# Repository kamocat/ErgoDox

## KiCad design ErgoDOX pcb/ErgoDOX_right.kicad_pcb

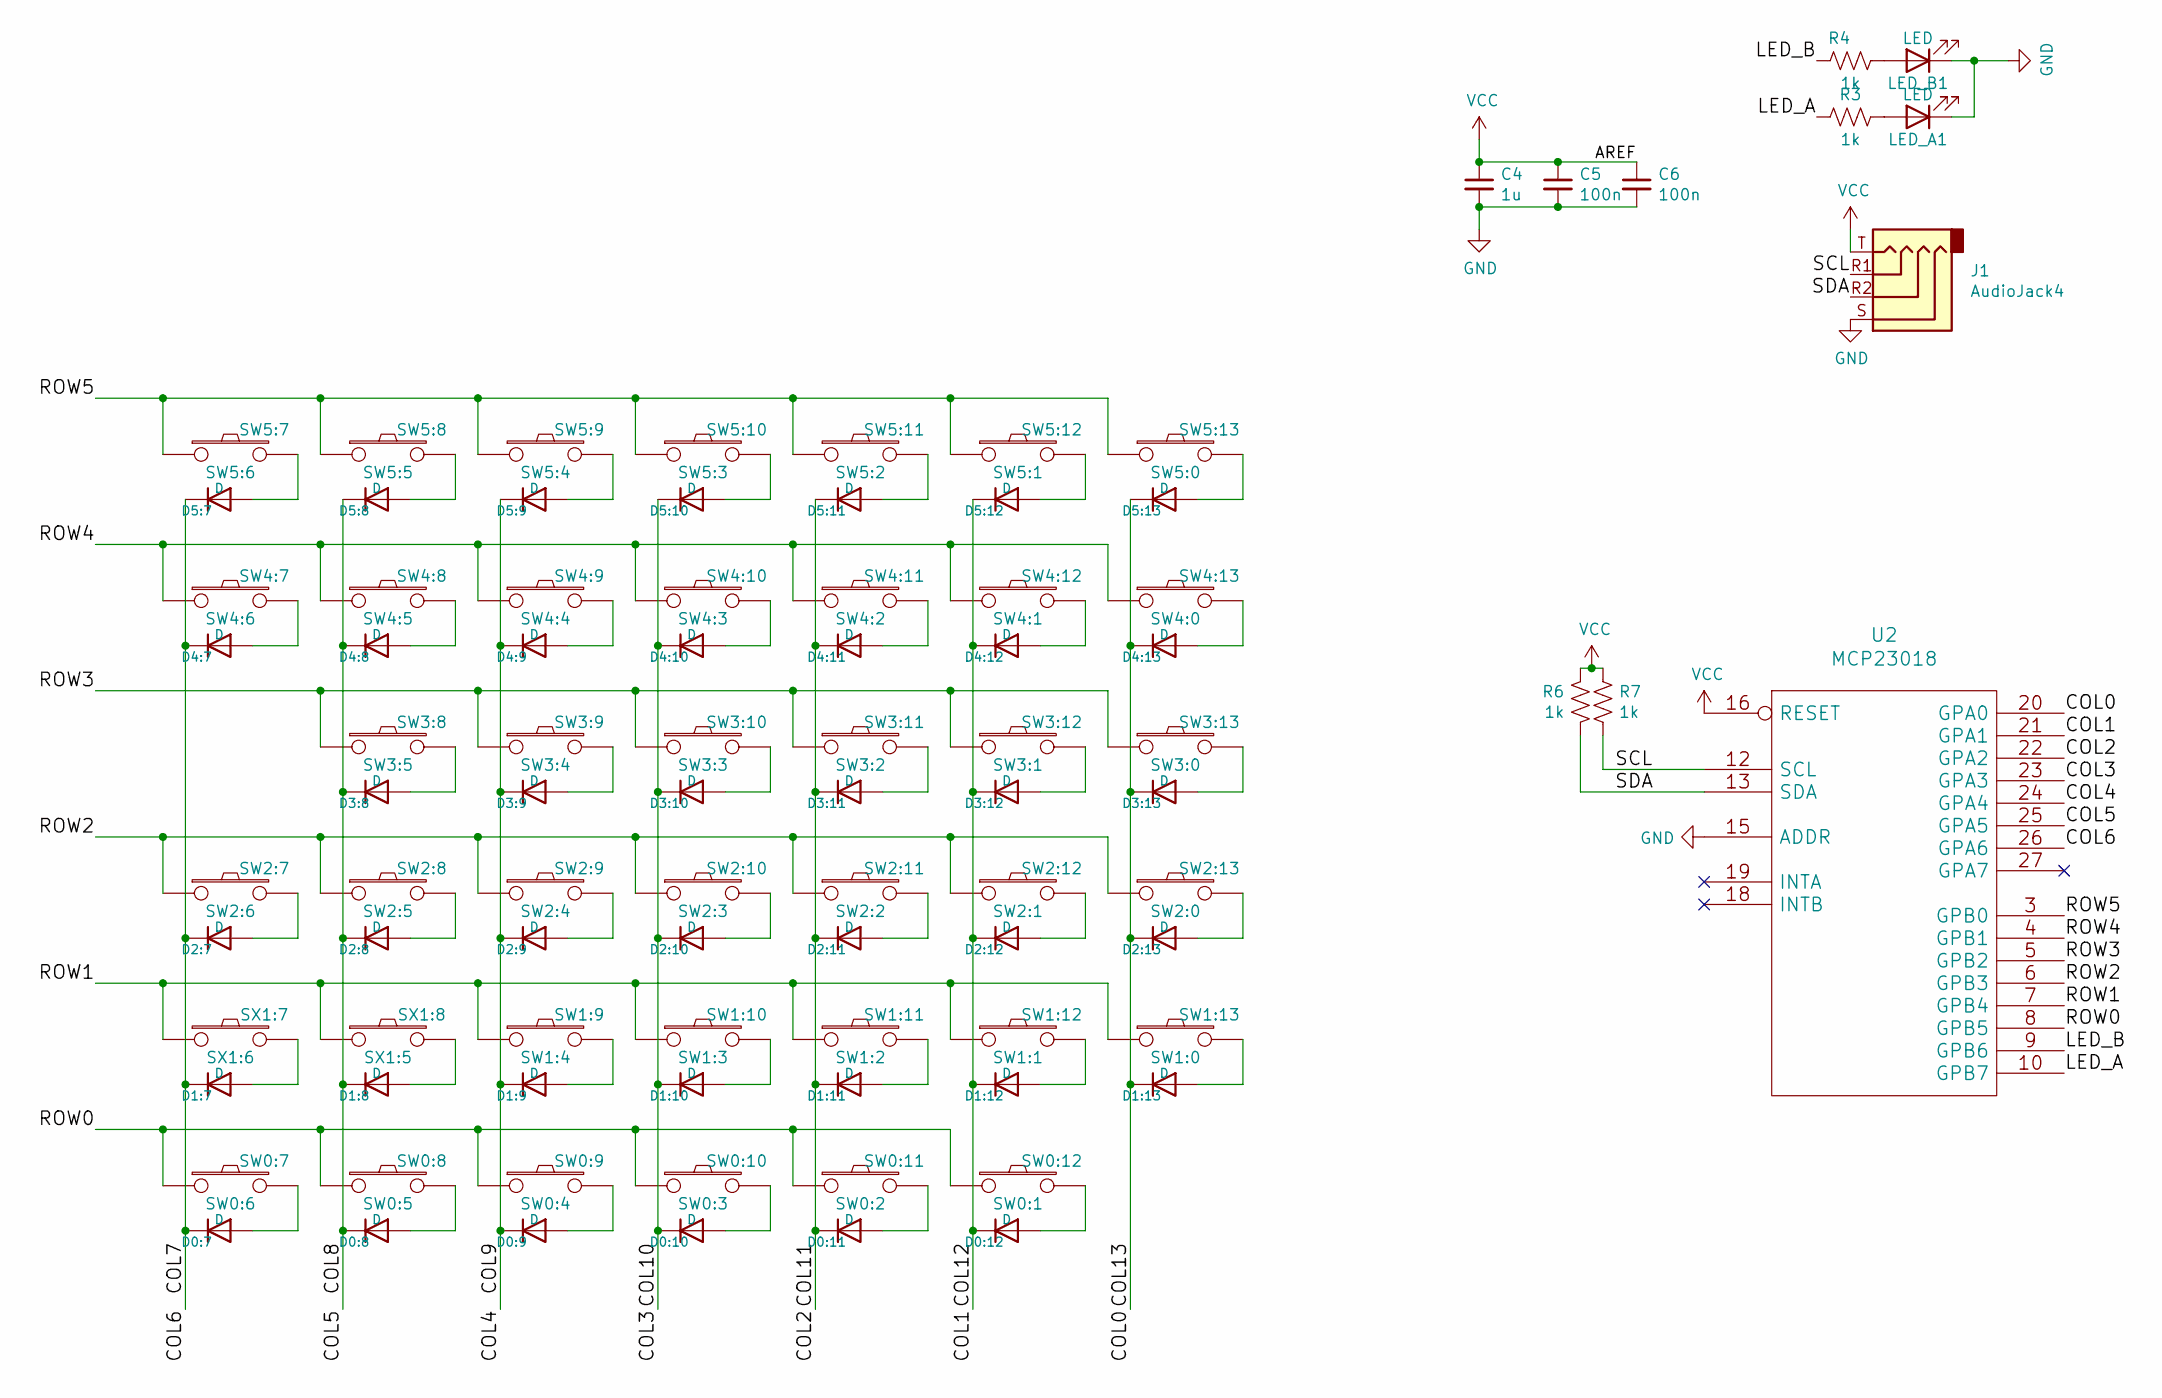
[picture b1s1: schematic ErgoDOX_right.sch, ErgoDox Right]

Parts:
C4: 1u; C_0603
C5, C6: 100n; C_0603
D0:7, D0:8, D0:9, D0:10, D0:11, D0:12, D1:7, D1:8, D1:9, D1:10, D1:11, D1:12, D1:13, D2:7, D2:8, D2:9, D2:10, D2:11, D2:12, D2:13, D3:8, D3:9, D3:10, D3:11, D3:12, D3:13, D4:7, D4:8, D4:9, D4:10, D4:11, D4:12, D4:13, D5:7, D5:8, D5:9, D5:10, D5:11, D5:12, D5:13: D; D_SOD-123
J1: AudioJack4; 54-00174
LED_A1: LED; LED_0603
LED_B1: LED; LED_0603
R3, R4, R6, R7: 1k; R_0603
SW0:7: SW0:6; MX_TOP
SW0:8: SW0:5; MX_TOP
SW0:9: SW0:4; MX_TOP
SW0:10: SW0:3; MX_TOP
SW0:11: SW0:2; MX_TOP
SW0:12: SW0:1; MX_TOP
SW1:9: SW1:4; MX_TOP
SW1:10: SW1:3; MX_TOP
SW1:11: SW1:2; MX_TOP
SW1:12: SW1:1; MX_TOP
SW1:13: SW1:0; MX_TOP
SW2:7: SW2:6; MX_TOP
SW2:8: SW2:5; MX_TOP
SW2:9: SW2:4; MX_TOP
SW2:10: SW2:3; MX_TOP
SW2:11: SW2:2; MX_TOP
SW2:12: SW2:1; MX_TOP
SW2:13: SW2:0; MX_TOP
SW3:8: SW3:5; MX_TOP
SW3:9: SW3:4; MX_TOP
SW3:10: SW3:3; MX_TOP
SW3:11: SW3:2; MX_TOP
SW3:12: SW3:1; MX_TOP
SW3:13: SW3:0; MX_TOP
SW4:7: SW4:6; MX_TOP
SW4:8: SW4:5; MX_TOP
SW4:9: SW4:4; MX_TOP
SW4:10: SW4:3; MX_TOP
SW4:11: SW4:2; MX_TOP
SW4:12: SW4:1; MX_TOP
SW4:13: SW4:0; MX_TOP
SW5:7: SW5:6; MX_TOP
SW5:8: SW5:5; MX_TOP
SW5:9: SW5:4; MX_TOP
SW5:10: SW5:3; MX_TOP
SW5:11: SW5:2; MX_TOP
SW5:12: SW5:1; MX_TOP
SW5:13: SW5:0; MX_TOP
SX1:7: SX1:6; MX_TOP
SX1:8: SX1:5; MX_TOP
U2: MCP23018; SOIC-28W_7.5x17.9mm_Pitch1.27mm

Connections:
/COL0: D1:13.1 (K), D2:13.1 (K), D3:13.1 (K), D4:13.1 (K), D5:13.1 (K), U2.20 (GPA0)
/COL1: D0:12.1 (K), D1:12.1 (K), D2:12.1 (K), D3:12.1 (K), D4:12.1 (K), D5:12.1 (K), U2.21 (GPA1)
/COL4: D0:9.1 (K), D1:9.1 (K), D2:9.1 (K), D3:9.1 (K), D4:9.1 (K), D5:9.1 (K), U2.24 (GPA4)
/COL5: D0:8.1 (K), D1:8.1 (K), D2:8.1 (K), D3:8.1 (K), D4:8.1 (K), D5:8.1 (K), U2.25 (GPA5)
/COL6: D0:7.1 (K), D1:7.1 (K), D2:7.1 (K), D4:7.1 (K), D5:7.1 (K), U2.26 (GPA6)
/COL10: D0:10.1 (K), D1:10.1 (K), D2:10.1 (K), D3:10.1 (K), D4:10.1 (K), D5:10.1 (K), U2.23 (GPA3)
/COL11: D0:11.1 (K), D1:11.1 (K), D2:11.1 (K), D3:11.1 (K), D4:11.1 (K), D5:11.1 (K), U2.22 (GPA2)
/LED_A: R3.1, U2.10 (GPB7)
/LED_B: R4.1, U2.9 (GPB6)
/ROW0: SW0:7.1, SW0:8.1, SW0:9.1, SW0:10.1, SW0:11.1, SW0:12.1, U2.8 (GPB5)
/ROW1: SW1:9.1, SW1:10.1, SW1:11.1, SW1:12.1, SW1:13.1, SX1:7.1, SX1:8.1, U2.7 (GPB4)
/ROW2: SW2:7.1, SW2:8.1, SW2:9.1, SW2:10.1, SW2:11.1, SW2:12.1, SW2:13.1, U2.6 (GPB3)
/ROW3: SW3:8.1, SW3:9.1, SW3:10.1, SW3:11.1, SW3:12.1, SW3:13.1, U2.5 (GPB2)
/ROW4: SW4:7.1, SW4:8.1, SW4:9.1, SW4:10.1, SW4:11.1, SW4:12.1, SW4:13.1, U2.4 (GPB1)
/ROW5: SW5:7.1, SW5:8.1, SW5:9.1, SW5:10.1, SW5:11.1, SW5:12.1, SW5:13.1, U2.3 (GPB0)
/SCL: J1.R1, R7.2, U2.12 (SCL)
/SDA: J1.R2, R6.1, U2.13 (SDA)
GND: C4.2, C5.2, C6.2, J1.S, LED_A1.1 (K), LED_B1.1 (K), U2.1 (GND), U2.15 (ADDR)
unnamed: D0:7.2 (A), SW0:7.2
unnamed: D0:8.2 (A), SW0:8.2
unnamed: D0:9.2 (A), SW0:9.2
unnamed: D0:10.2 (A), SW0:10.2
unnamed: D0:11.2 (A), SW0:11.2
unnamed: D0:12.2 (A), SW0:12.2
unnamed: D1:7.2 (A), SX1:7.2
unnamed: D1:8.2 (A), SX1:8.2
unnamed: D1:9.2 (A), SW1:9.2
unnamed: D1:10.2 (A), SW1:10.2
unnamed: D1:11.2 (A), SW1:11.2
unnamed: D1:12.2 (A), SW1:12.2
unnamed: D1:13.2 (A), SW1:13.2
unnamed: D2:7.2 (A), SW2:7.2
unnamed: D2:8.2 (A), SW2:8.2
unnamed: D2:9.2 (A), SW2:9.2
unnamed: D2:10.2 (A), SW2:10.2
unnamed: D2:11.2 (A), SW2:11.2
unnamed: D2:12.2 (A), SW2:12.2
unnamed: D2:13.2 (A), SW2:13.2
unnamed: D3:8.2 (A), SW3:8.2
unnamed: D3:9.2 (A), SW3:9.2
unnamed: D3:10.2 (A), SW3:10.2
unnamed: D3:11.2 (A), SW3:11.2
unnamed: D3:12.2 (A), SW3:12.2
unnamed: D3:13.2 (A), SW3:13.2
unnamed: D4:7.2 (A), SW4:7.2
unnamed: D4:8.2 (A), SW4:8.2
unnamed: D4:9.2 (A), SW4:9.2
unnamed: D4:10.2 (A), SW4:10.2
unnamed: D4:11.2 (A), SW4:11.2
unnamed: D4:12.2 (A), SW4:12.2
unnamed: D4:13.2 (A), SW4:13.2
unnamed: D5:7.2 (A), SW5:7.2
unnamed: D5:8.2 (A), SW5:8.2
unnamed: D5:9.2 (A), SW5:9.2
unnamed: D5:10.2 (A), SW5:10.2
unnamed: D5:11.2 (A), SW5:11.2
unnamed: D5:12.2 (A), SW5:12.2
unnamed: D5:13.2 (A), SW5:13.2
unnamed: LED_A1.2 (A), R3.2
unnamed: LED_B1.2 (A), R4.2
VCC: C4.1, C5.1, C6.1, J1.T, R6.2, R7.1, U2.11 (VCC), U2.16 (RESET)

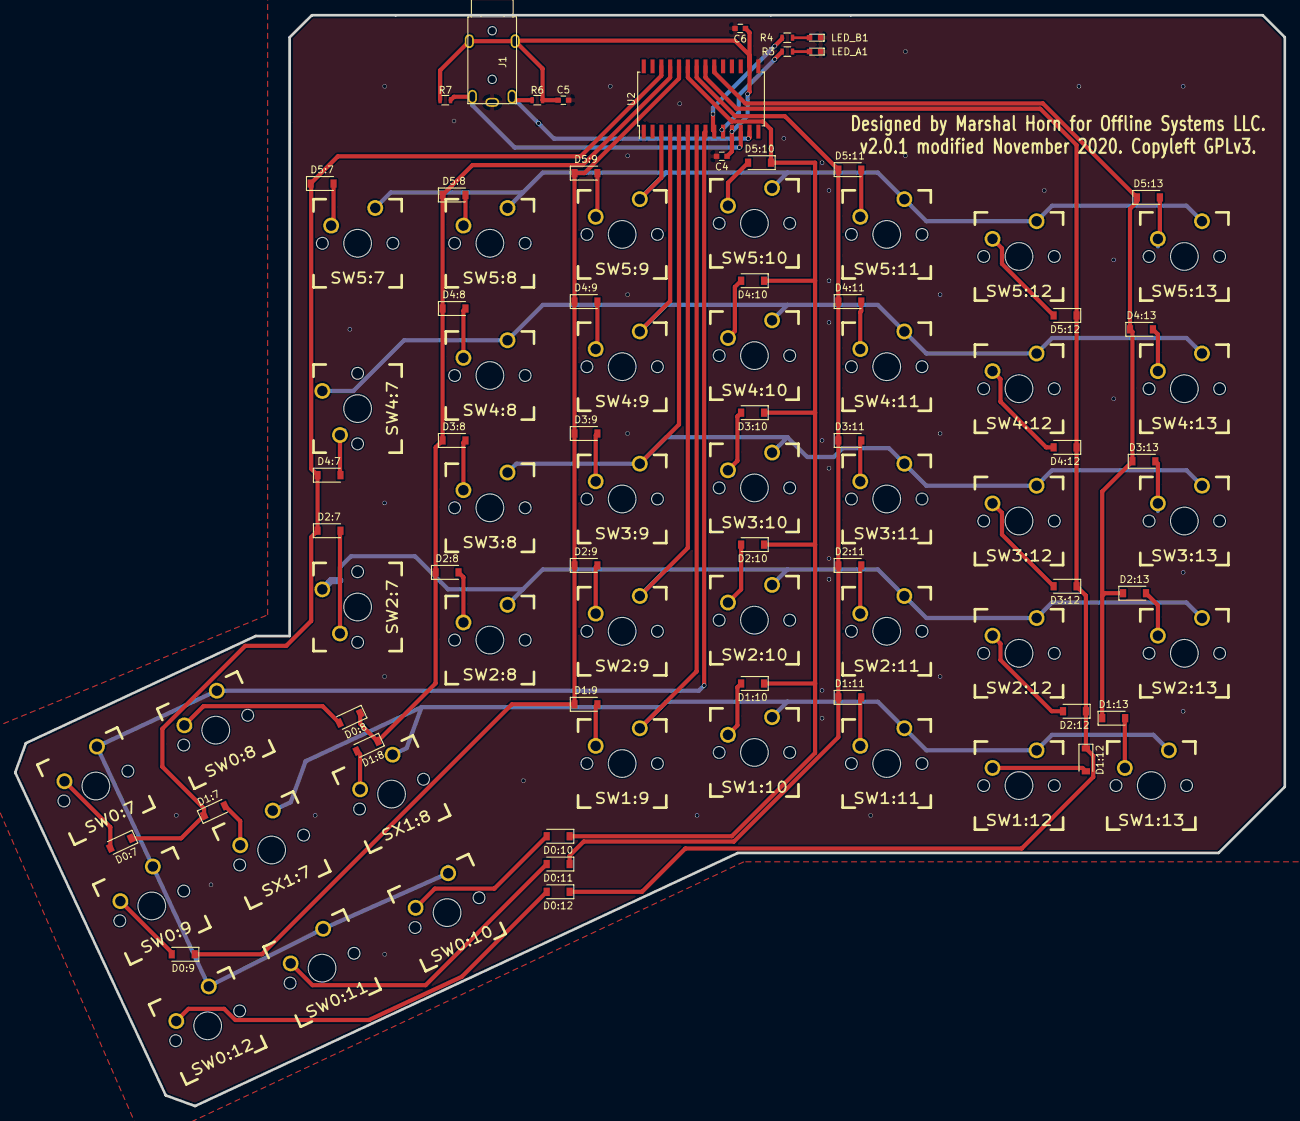
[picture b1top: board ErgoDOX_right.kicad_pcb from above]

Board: 2 copper layers, 182.8 x 157.1 mm, 91 parts (0 on the bottom side), 61 nets.

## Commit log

2020-09-17 Replaced teensy with atmega
    Imported project into new version of KiCad
    Initial routing of traces is done
    Switch footprints need some investigation - overlap is throwing design rule errors
2020-10-03 migrated to newer KiCAD
2020-10-05 Changed footprints for easier manufacturability
    * Diodes are now surface-mount. Don't buy the switches with built-in diodes.
    * Changed processor from at90usb1286 to atmega32u4 (due to availability and cost)
    * Renamed footprint library
2020-10-08 Placed diodes, started routing
2020-10-08 Split boards into LH and RH
2020-10-09 finished LH routing
2020-10-09 USB breakout draft
2020-10-09 Routed RH board
2020-10-09 Updated USB footprints
2020-10-09 Removed old gerber files
2020-10-12 Added revision, generated gerbers
2020-10-12 Corrected revision number
2020-10-16 Removed soldermask clearance
    Re-generated gerbers for left PCB
    Added BOM and placement file for left PCB
2020-10-27 Added BOM and CPL files for JLC assembly
2020-11-01 Switched MCP23018 to SOIC package
2020-11-01 Fixed position file headers for JLC

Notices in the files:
ErgoDOX pcb/ErgoDOX_right.kicad_pcb:
v2.0.1 modified November 2020. Copyleft GPLv3.
